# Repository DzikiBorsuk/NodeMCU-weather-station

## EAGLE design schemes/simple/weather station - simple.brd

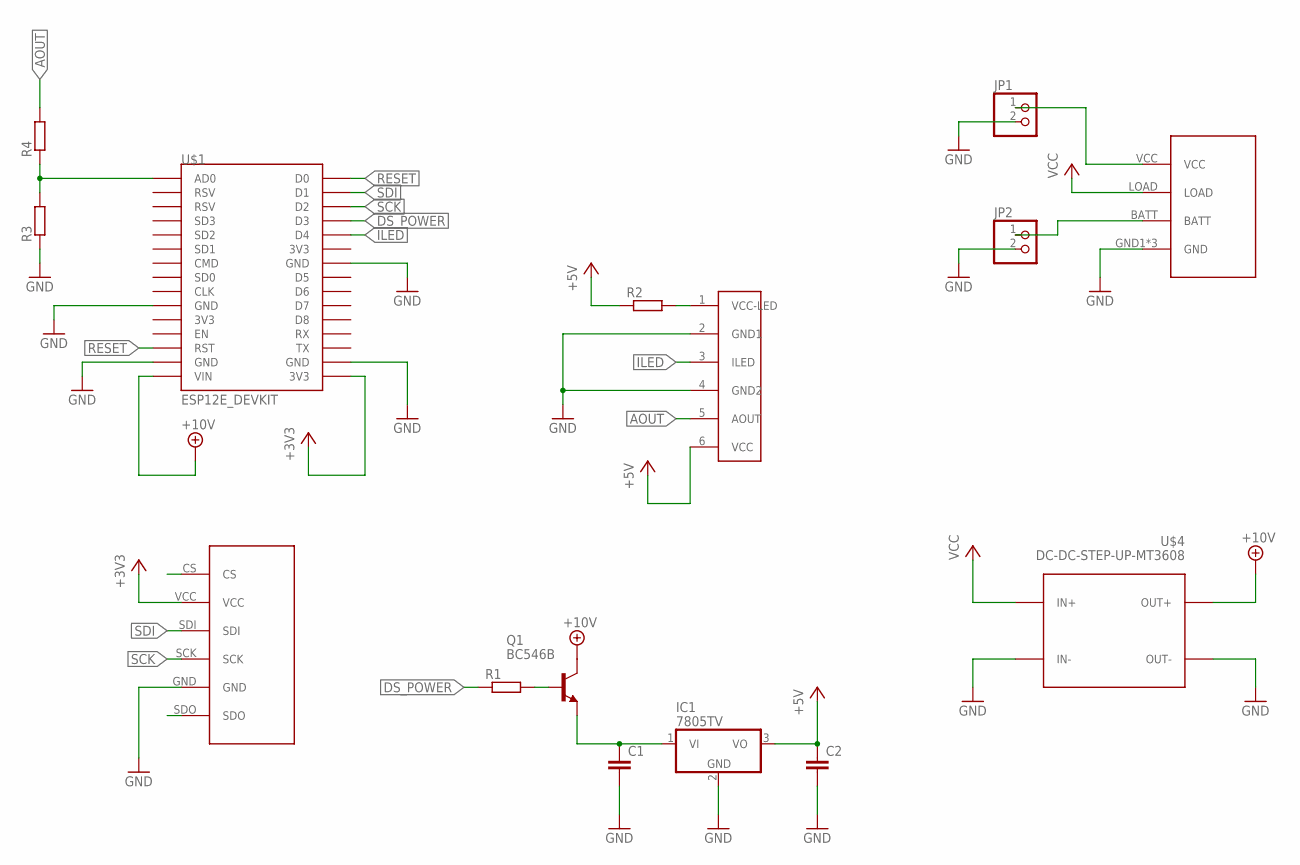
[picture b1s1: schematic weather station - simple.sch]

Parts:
C1, C2: C-EU025-024X044; C025-024X044
IC1: 7805TV; TO220V
JP1, JP2: PINHD-1X2; 1X02
Q1: BC546B; TO92-EBC
R1, R2, R3, R4: R-EU_0207/10; 0207/10
U$1: ESP12E_DEVKIT
U$2: ADAFRUIT_SOLARCHARGER
U$3: BME680_BLUEDOT; 1X06
U$4: DC-DC-STEP-UP-MT3608
U$5: DUST_SENSOR

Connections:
+3V3: U$1.3V3@2 (3V3), U$3.VCC
+5V: C2.1, IC1.3 (VO), R2.1, U$5.6 (VCC)
+10V: Q1.C, U$1.VIN, U$4.OUT+
AOUT: R4.2, U$5.5 (AOUT)
DS_POWER: R1.1, U$1.D3
GND: C1.2, C2.2, IC1.2 (GND), JP1.2, JP2.2, R3.1, U$1.GND@0 (GND), U$1.GND@1 (GND), U$1.GND@2 (GND), U$1.GND@3 (GND), U$2.GND1 (GND), U$2.GND2 (GND), U$2.GND3 (GND), U$3.GND, U$4.IN-, U$4.OUT-, U$5.2 (GND1), U$5.4 (GND2)
ILED: U$1.D4, U$5.3 (ILED)
unnamed: JP2.1, U$2.BATT
unnamed: JP1.1, U$2.VCC
unnamed: C1.1, IC1.1 (VI), Q1.E
unnamed: Q1.B, R1.2
unnamed: R2.2, U$5.1 (VCC-LED)
unnamed: R3.2, R4.1, U$1.AD0
RESET: U$1.D0, U$1.RST
SCK: U$1.D2, U$3.SCK
SDI: U$1.D1, U$3.SDI
VCC: U$2.LOAD, U$4.IN+

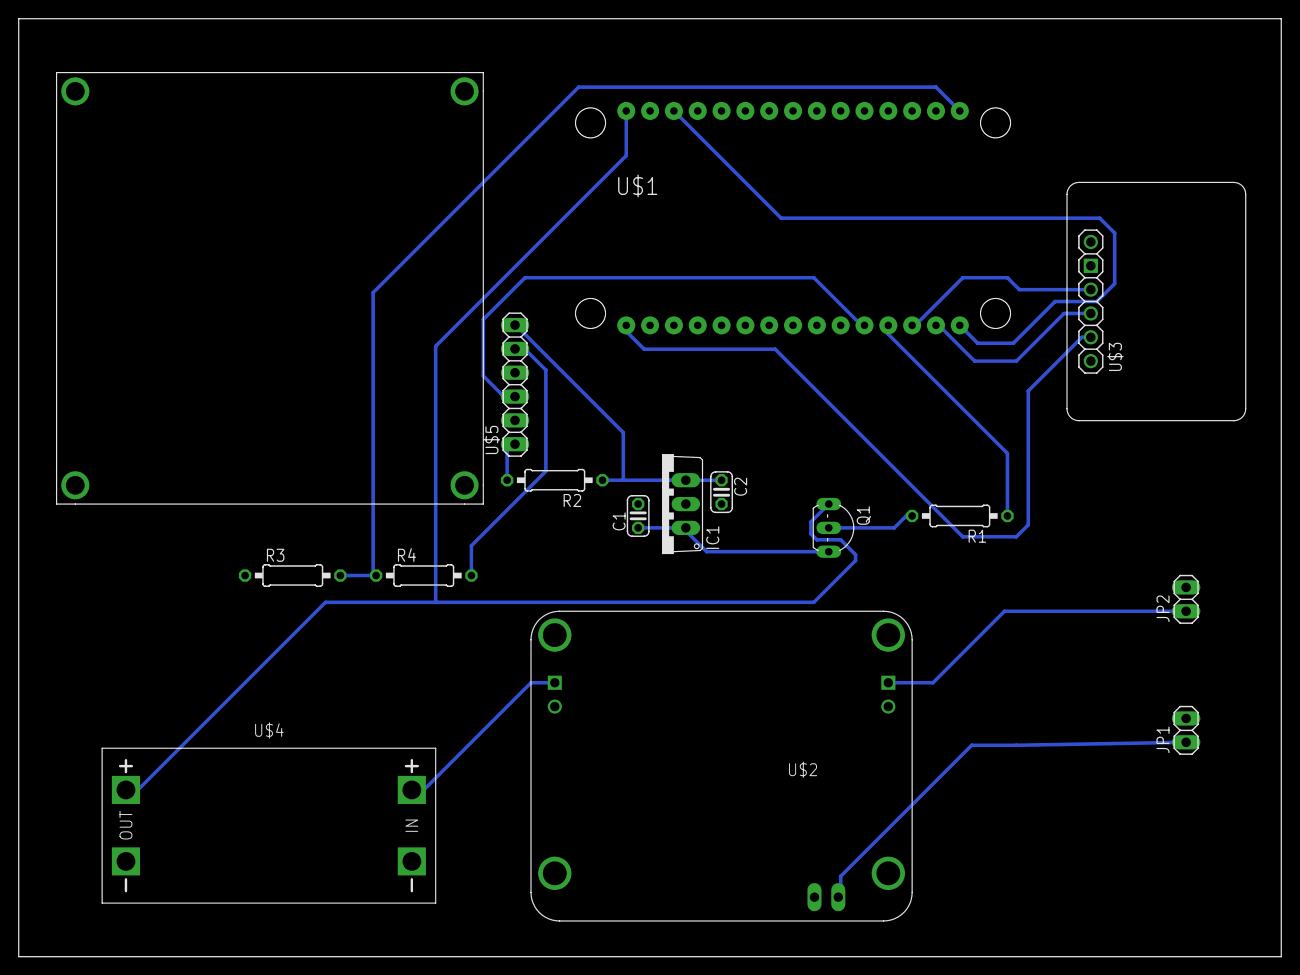
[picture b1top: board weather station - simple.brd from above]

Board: 2 copper layers, 134.6 x 100.0 mm, 15 parts (0 on the bottom side), 17 nets.

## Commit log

2018-06-21 init
2018-06-21 git ignore update
2018-06-21 OTA init
2018-06-22 OTA update
2018-07-30 z MQTT alfa
2018-07-30 publikowanie MQTT dla wszystkich sensorow
2018-07-30 usuniecie paru niepotrzebnych linijek, dodanie DeepSleepu(ale nie dziala jezscze perfekcyjnie)
2018-07-31 simple PCB prototype
2018-07-31 dodanie forceSleepWake() i komentarzy sprawdzajacacych
2018-07-31 forcewakesleep + pare komentarzy, proba naprawy mqtt do altitude
2018-07-31 dodanie odliczania czasu
2018-08-01 zmiana w vcxproj!
2018-08-02 przesylanie wiadomosci w JSON
2018-08-03 PCB scheme update
2018-08-03 dust sensor, wysylanie wszystkiego json!!
2018-08-06 wersja z wyslaniem poprzez HTTP na strone!
2018-08-07 z wysylaniem na strone w local hoscie
2018-08-07 wysylaniem przez http rowniez dla dust sensor (w htcdocs jest to sensorDust), dodanie paru komentarzy i usuniecie czesci kodu, w 95% gotowy projekt
2018-08-23 delay byl usuniety zara za publikowaniem w weatherstation.ino, ale juz naprawione, zakomentowany jest dust sensor!
2018-09-20 ze strona
2018-09-20 Praktycznie caly projekt gotowy, tylko dust sensor odwala.
2018-09-21 php server
2018-09-23 finished website
2018-09-24 Final version
2018-09-24 website update
2018-09-24 last fix

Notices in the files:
parts and their libraries:
diy-modules: Released under the Creative Commons Attribution 4.0 International License: http://creativecommons.org/licenses/by/4.0
